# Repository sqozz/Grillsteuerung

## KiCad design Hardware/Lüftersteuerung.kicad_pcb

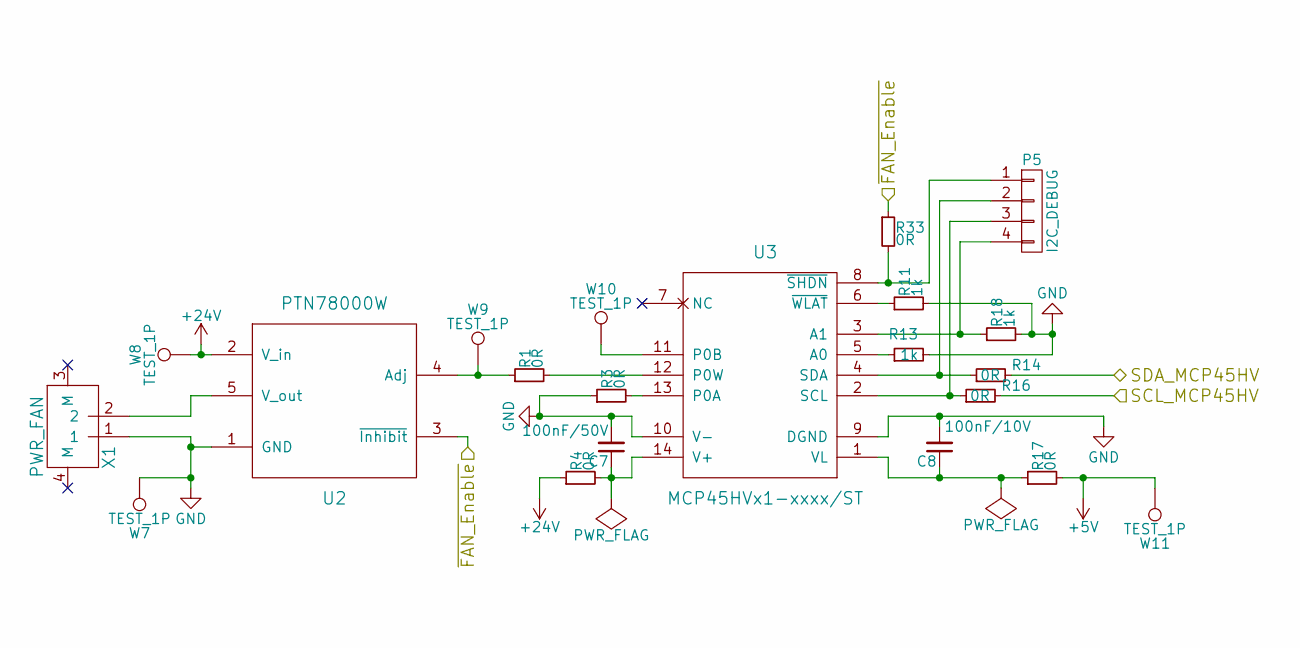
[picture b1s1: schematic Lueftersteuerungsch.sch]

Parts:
C7: 100nF/50V; C_0603
C8: 100nF/10V; C_0603
P5: I2C_DEBUG; Pin_Header_Straight_1x04
R1, R3, R4, R14, R16, R17, R33: 0R; R_0603
R11, R13, R18: 1k; R_0603
U2: PTN78000W; PTN78000H
U3: MCP45HVx1-xxxx/ST; TSSOP-14_4.4x5mm_Pitch0.65mm
W7, W8, W9, W10, W11: TEST_1P; Measurement_Point_Round-SMD-Pad_Small
X1: PWR_FAN; 2-1445057-2

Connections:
+5V: R17.2, W11.1; also elsewhere on the board
+24V: R4.1, U2.2 (V_in), W8.1; also elsewhere on the board
/Lüftersteuerung/SCL_MCP45HV: R16.2; also elsewhere on the board
/Lüftersteuerung/SDA_MCP45HV: R14.2; also elsewhere on the board
/Lüftersteuerung/~FAN_Enable: R33.1, U2.3 (~Inhibit); also elsewhere on the board
GND: C7.2, C8.2, R3.1, R11.2, R13.2, R18.2, U2.1 (GND), U3.9 (DGND), U3.10 (V-), W7.1, X1.1; also elsewhere on the board
unnamed: C7.1, R4.2, U3.14 (V+)
unnamed: C8.1, R17.1, U3.1 (VL)
unnamed: P5.1, R33.2, U3.8 (~SHDN)
unnamed: P5.2, R14.1, U3.4 (SDA)
unnamed: P5.3, R16.1, U3.2 (SCL)
unnamed: P5.4, R18.1, U3.3 (A1)
unnamed: R1.1, U2.4 (Adj), W9.1
unnamed: R1.2, U3.12 (P0W)
unnamed: R3.2, U3.13 (P0A)
unnamed: R11.1, U3.6 (~WLAT)
unnamed: R13.1, U3.5 (A0)
unnamed: U2.5 (V_out), X1.2
unnamed: U3.11 (P0B), W10.1

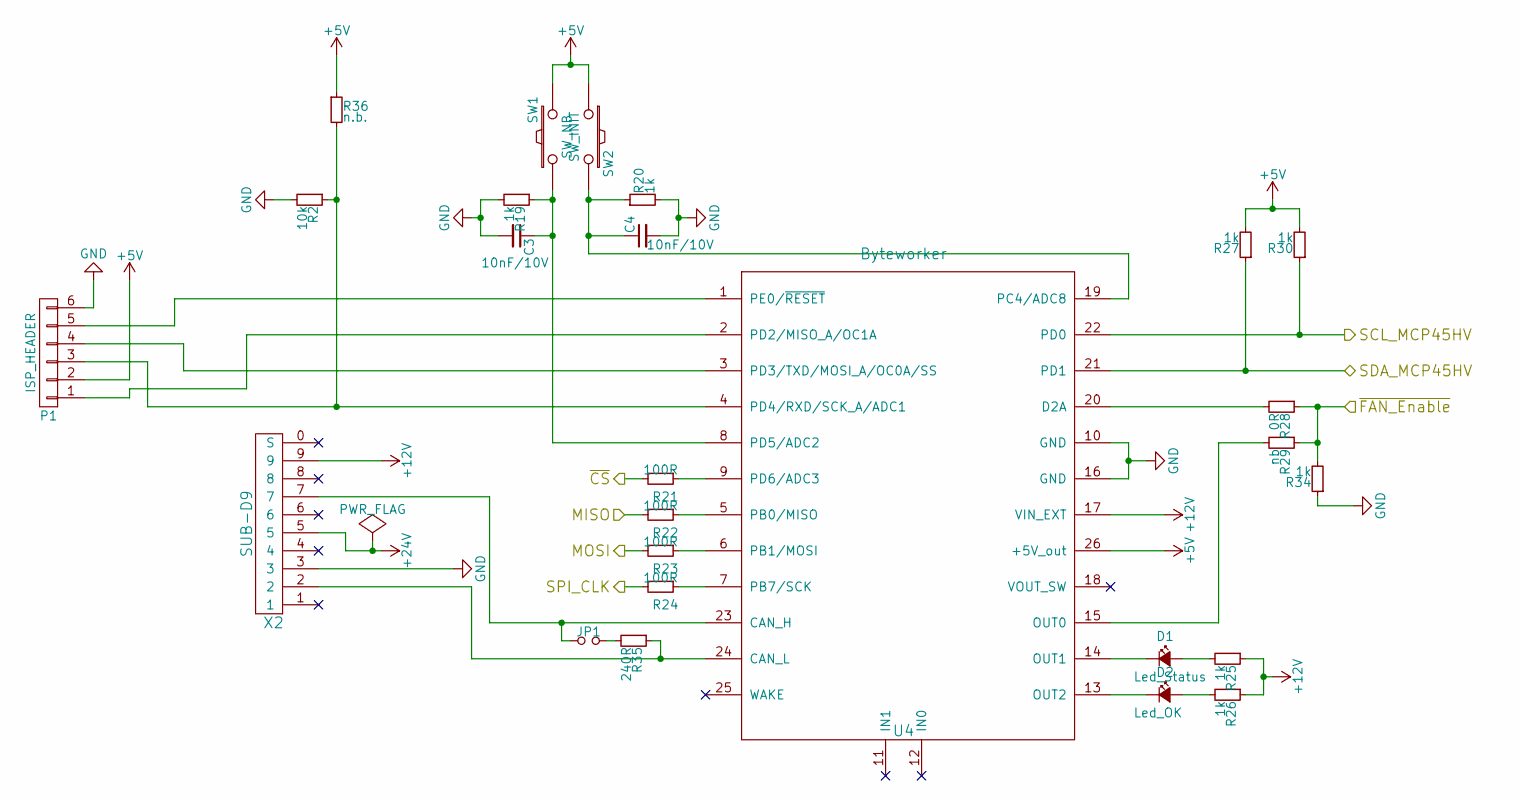
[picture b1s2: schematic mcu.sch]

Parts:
C3, C4: 10nF/10V; C_0603
D1: Led_Status; LED_D3.0mm
D2: Led_OK; LED_D3.0mm
JP1: Jumper_NO_Small; Pin_Header_Straight_1x02
P1: ISP_HEADER; Pin_Header_Straight_2x03
R2: 10k; R_0603
R19, R20, R25, R26, R27, R30, R34: 1k; R_0603
R21, R22, R23, R24: 100R; R_0603
R28: 0R; R_0603
R29: nb; R_0603
R35: 240R; R_0603_HandSoldering
R36: n.b.; R_0603
SW1: SW_NB; SW_Tactile_SPST_Angled
SW2: SW_INIT; SW_Tactile_SPST_Angled
U4: Byteworker; byteworker
X2: SUB-D9; DB9M_CI

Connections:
+5V: P1.2, R27.2, R30.2, R36.1, SW1.2, SW2.1, U4.26 (+5V_out); also elsewhere on the board
+12V: R25.1, R26.1, U4.17 (VIN_EXT), X2.9
+24V: X2.5; also elsewhere on the board
/Lüftersteuerung/SCL_MCP45HV: R30.1, U4.22 (PD0); also elsewhere on the board
/Lüftersteuerung/SDA_MCP45HV: R27.1, U4.21 (PD1); also elsewhere on the board
/Lüftersteuerung/~FAN_Enable: R28.1, R29.1, R34.2; also elsewhere on the board
/MCU/MISO: R22.2; also elsewhere on the board
/MCU/MOSI: R23.2; also elsewhere on the board
/MCU/SPI_CLK: R24.2; also elsewhere on the board
/MCU/~CS: R21.2; also elsewhere on the board
GND: C3.2, C4.2, P1.6, R2.2, R19.2, R20.2, R34.1, U4.10 (GND), U4.16 (GND), X2.3; also elsewhere on the board
unnamed: C3.1, R19.1, SW1.1, U4.8 (PD5/ADC2)
unnamed: C4.1, R20.1, SW2.2, U4.19 (PC4/ADC8)
unnamed: D1.1 (K), U4.14 (OUT1)
unnamed: D1.2 (A), R25.2
unnamed: D2.1 (K), U4.13 (OUT2)
unnamed: D2.2 (A), R26.2
unnamed: JP1.1, U4.23 (CAN_H), X2.7
unnamed: JP1.2, R35.2
unnamed: P1.1, U4.2 (PD2/MISO_A/OC1A)
unnamed: P1.3, R2.1, R36.2, U4.4 (PD4/RXD/SCK_A/ADC1)
unnamed: P1.4, U4.3 (PD3/TXD/MOSI_A/OC0A/SS)
unnamed: P1.5, U4.1 (PE0/~RESET)
unnamed: R21.1, U4.9 (PD6/ADC3)
unnamed: R22.1, U4.5 (PB0/MISO)
unnamed: R23.1, U4.6 (PB1/MOSI)
unnamed: R24.1, U4.7 (PB7/SCK)
unnamed: R28.2, U4.20 (D2A)
unnamed: R29.2, U4.15 (OUT0)
unnamed: R35.1, U4.24 (CAN_L), X2.2

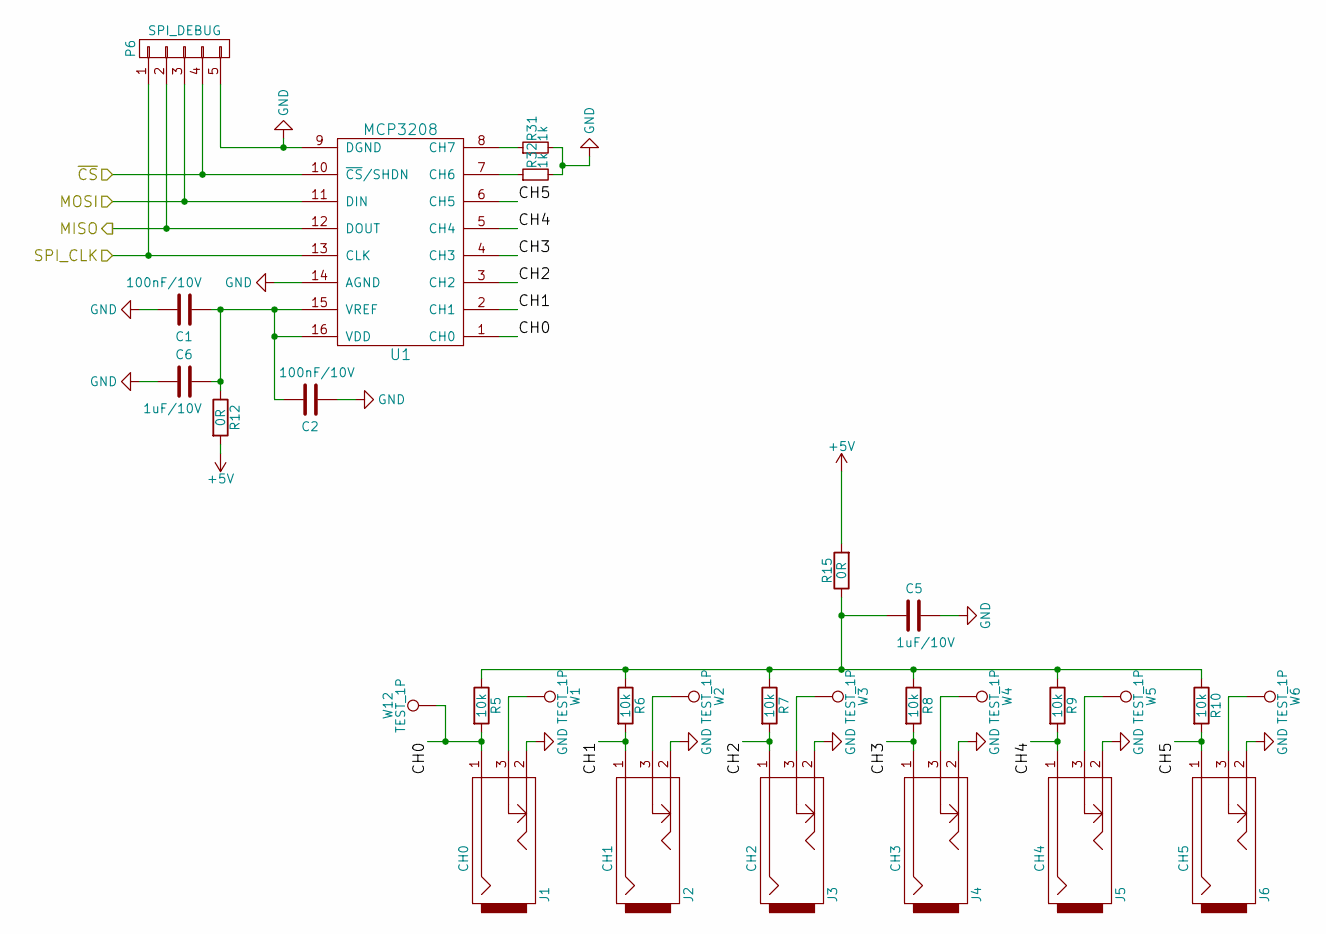
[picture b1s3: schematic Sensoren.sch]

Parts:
C1, C2: 100nF/10V; C_0603
C5, C6: 1uF/10V; C_0603
J1: CH0; MJ-2508
J2: CH1; MJ-2508
J3: CH2; MJ-2508
J4: CH3; MJ-2508
J5: CH4; MJ-2508
J6: CH5; MJ-2508
P6: SPI_DEBUG; Pin_Header_Straight_1x05
R5, R6, R7, R8, R9, R10: 10k; R_0603
R12, R15: 0R; R_0603
R31, R32: 1k; R_0603
U1: MCP3208; SO-16-N
W1, W2, W3, W4, W5, W6, W12: TEST_1P; Measurement_Point_Round-SMD-Pad_Small

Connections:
+5V: R12.2, R15.2; also elsewhere on the board
/MCU/MISO: P6.2, U1.12 (DOUT); also elsewhere on the board
/MCU/MOSI: P6.3, U1.11 (DIN); also elsewhere on the board
/MCU/SPI_CLK: P6.1, U1.13 (CLK); also elsewhere on the board
/MCU/~CS: P6.4, U1.10 (~CS~/SHDN); also elsewhere on the board
/Sensoren/CH0: J1.1, R5.2, U1.1 (CH0), W12.1
/Sensoren/CH1: J2.1, R6.2, U1.2 (CH1)
/Sensoren/CH2: J3.1, R7.2, U1.3 (CH2)
/Sensoren/CH3: J4.1, R8.2, U1.4 (CH3)
/Sensoren/CH4: J5.1, R9.2, U1.5 (CH4)
/Sensoren/CH5: J6.1, R10.2, U1.6 (CH5)
GND: C1.1, C2.2, C5.1, C6.1, J1.2, J2.2, J3.2, J4.2, J5.2, J6.2, P6.5, R31.2, R32.2, U1.9 (DGND), U1.14 (AGND); also elsewhere on the board
unnamed: C1.2, C2.1, C6.2, R12.1, U1.15 (VREF), U1.16 (VDD)
unnamed: C5.2, R5.1, R6.1, R7.1, R8.1, R9.1, R10.1, R15.1
unnamed: J1.3, W1.1
unnamed: J2.3, W2.1
unnamed: J3.3, W3.1
unnamed: J4.3, W4.1
unnamed: J5.3, W5.1
unnamed: J6.3, W6.1
unnamed: R31.1, U1.8 (CH7)
unnamed: R32.1, U1.7 (CH6)

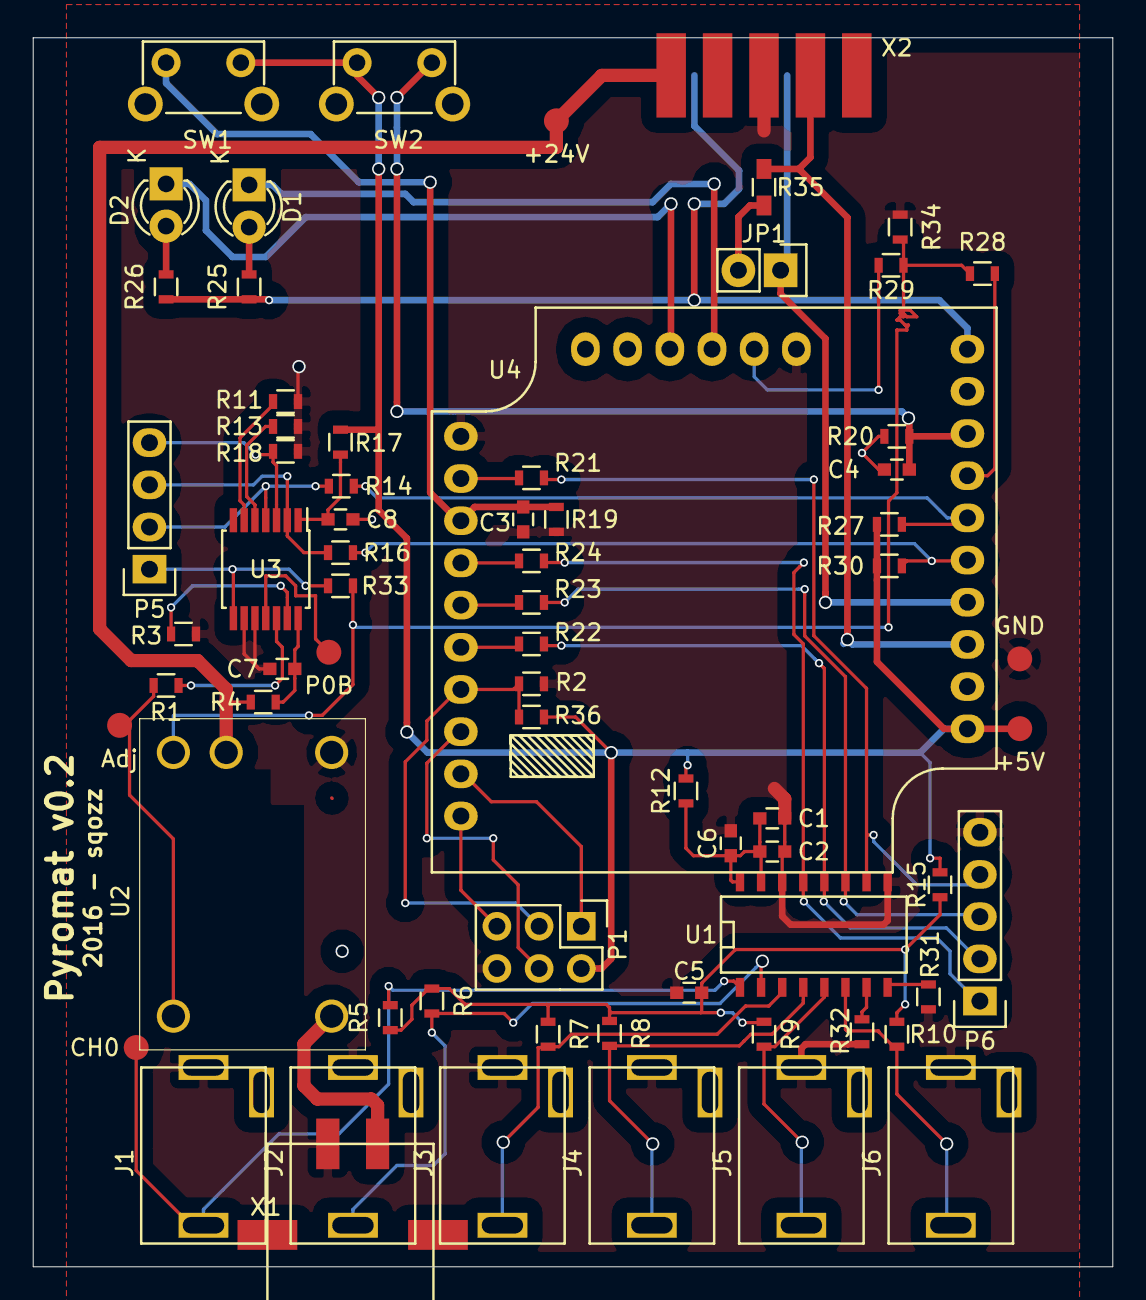
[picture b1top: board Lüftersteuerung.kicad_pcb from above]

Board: 2 copper layers, 65.0 x 74.0 mm, 70 parts (0 on the bottom side), 53 nets.

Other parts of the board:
GND: TEST_1P; Measurement_Point_Round-SMD-Pad_Small

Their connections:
GND: GND.1; also elsewhere on the board

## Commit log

2017-03-13 Add README.md
2017-03-13 Add hardware design
2017-03-13 Add README.md for byteworker software
2017-03-13 Add legacy "Lüfter" code
2017-03-13 Add legacy "Sensoren" code
2017-03-13 Add .gitignore
2017-03-13 Add UnitedFirmware for byteworker
    Can code is absolutely not duplicant in this repository… please ignore
    it for now. Thanks!
2017-03-13 Add frameworks and server code
2017-03-13 Add template, stylesheet and client code
2017-03-13 Update .gitignore for vim files
2017-03-13 Add first code for sync with master
2017-03-13 Improve sync with master
2017-03-13 Add resonse to commands
2017-03-13 Update enable/disable command desc.
2017-04-02 Add dynamic can id support
    This enables the boards (probe/fan boards) to request a can id from the
    master. This can id gets used to generate (e.g. by adding +1 for responses)
    a range in which the boards operate. The format of the commands has also
    changed, since they now support dynamic ranges too.
    Comments where added on a huge scale and in general this commit is way
    to huge… Anyway, it fixes a lot of stuff!
2017-04-04 Add vim config to WebUI/main.py
2017-04-05 don hinzufügt
2017-05-04 Revert me soon…
2017-05-04 Revert me too, please
2017-10-11 fixed all known hardware issues
